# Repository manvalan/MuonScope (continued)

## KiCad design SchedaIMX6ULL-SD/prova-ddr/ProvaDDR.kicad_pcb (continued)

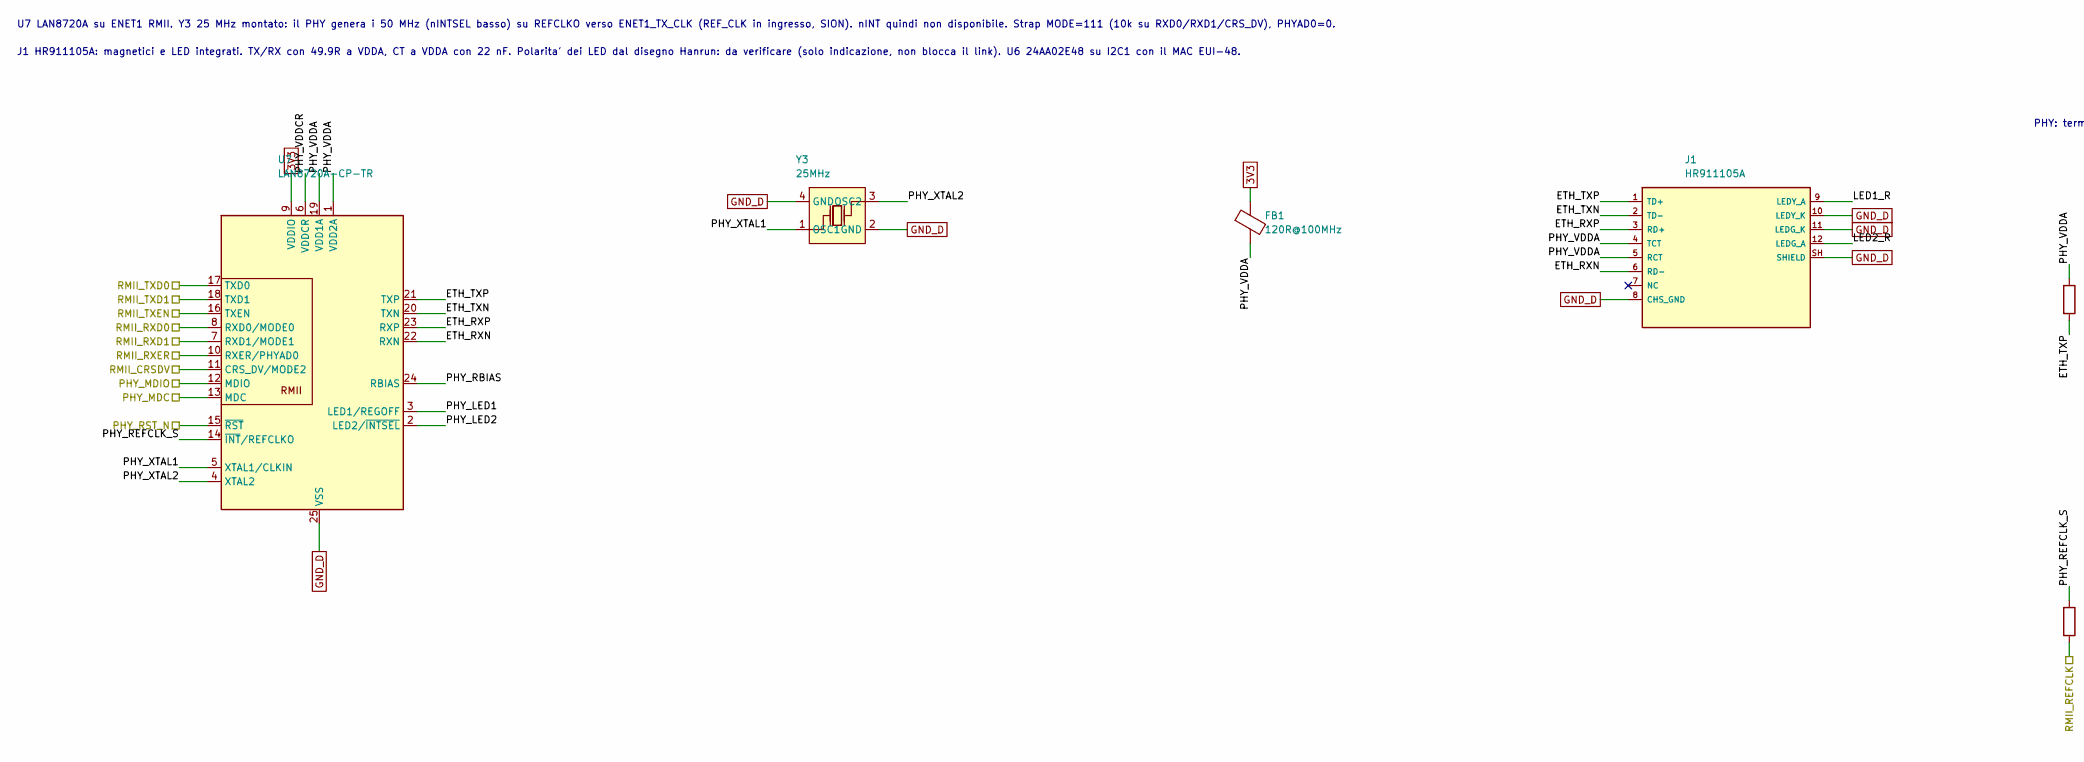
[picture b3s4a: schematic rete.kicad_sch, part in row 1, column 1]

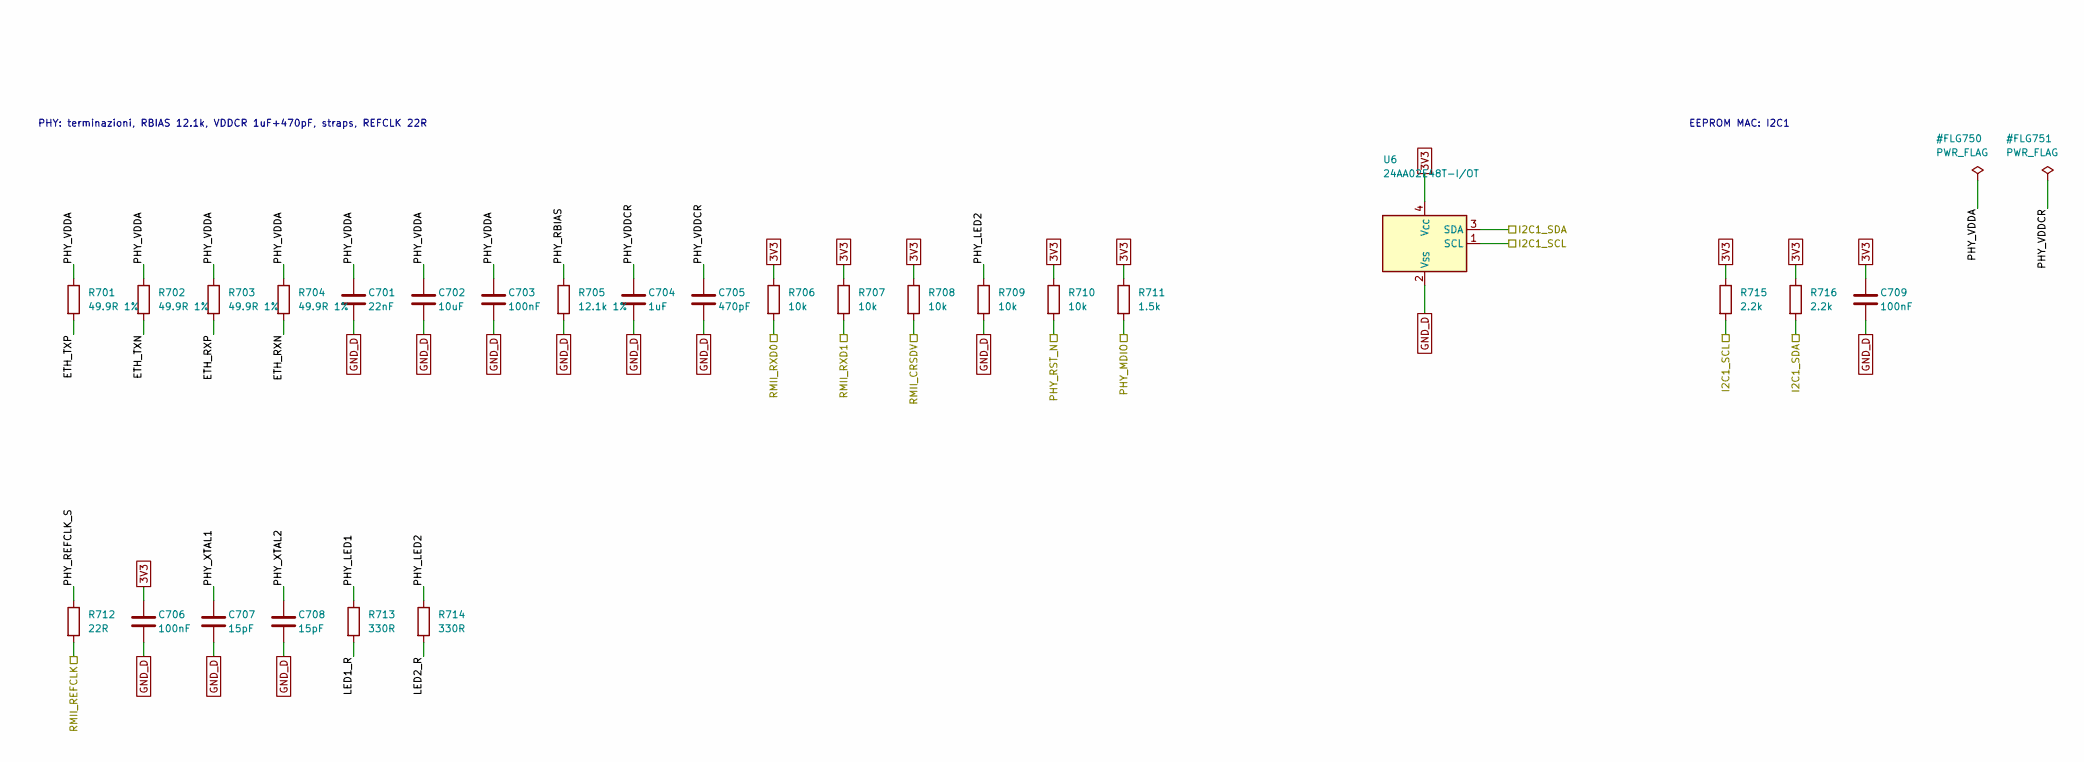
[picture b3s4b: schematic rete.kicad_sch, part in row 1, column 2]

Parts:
C701: 22nF; C_0603_1608Metric
C702: 10uF; C_0805_2012Metric
C703, C706, C709: 100nF; C_0603_1608Metric
C704: 1uF; C_0603_1608Metric
C705: 470pF; C_0603_1608Metric
C707, C708: 15pF; C_0603_1608Metric
FB1: 120R@100MHz; L_0603_1608Metric; MPN BLM18PG121SN1D
J1: HR911105A; RJ45_Hanrun_HR911105A_Horizontal; MPN HR911105A; LCSC C12074
R701, R702, R703, R704: 49.9R 1%; R_0603_1608Metric
R705: 12.1k 1%; R_0603_1608Metric
R706, R707, R708, R709, R710: 10k; R_0603_1608Metric
R711: 1.5k; R_0603_1608Metric
R712: 22R; R_0603_1608Metric
R713, R714: 330R; R_0603_1608Metric
R715, R716: 2.2k; R_0603_1608Metric
U6: 24AA02E48T-I/OT; SOT-23-5; MPN 24AA02E48T-I/OT; LCSC C38987
U7: LAN8720A-CP-TR; QFN-24-1EP_4x4mm_P0.5mm_EP2.6x2.6mm; MPN LAN8720A-CP-TR; LCSC C45223
Y3: 25MHz; CRYSTAL-SMD_4P-L3.2-W2.5-BL; MPN X322525MOB4SI; LCSC C9006

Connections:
3V3: C706.1, C709.1, FB1.1, R706.1, R707.1, R708.1, R710.1, R711.1, R715.1, R716.1, U6.4 (V_{CC}), U7.9 (VDDIO); also elsewhere on the board
/CPU/I2C1_SCL: R715.2, U6.1 (SCL); also elsewhere on the board
/CPU/I2C1_SDA: R716.2, U6.3 (SDA); also elsewhere on the board
/CPU/PHY_MDC: U7.13 (MDC); also elsewhere on the board
/CPU/PHY_MDIO: R711.2, U7.12 (MDIO); also elsewhere on the board
/CPU/PHY_RST_N: R710.2, U7.15 (~RST); also elsewhere on the board
/CPU/RMII_CRSDV: R708.2, U7.11 (CRS_DV/MODE2); also elsewhere on the board
/CPU/RMII_REFCLK: R712.2; also elsewhere on the board
/CPU/RMII_RXD0: R706.2, U7.8 (RXD0/MODE0); also elsewhere on the board
/CPU/RMII_RXD1: R707.2, U7.7 (RXD1/MODE1); also elsewhere on the board
/CPU/RMII_RXER: U7.10 (RXER/PHYAD0); also elsewhere on the board
/CPU/RMII_TXD0: U7.17 (TXD0); also elsewhere on the board
/CPU/RMII_TXD1: U7.18 (TXD1); also elsewhere on the board
/CPU/RMII_TXEN: U7.16 (TXEN); also elsewhere on the board
/Rete/ETH_RXN: J1.6 (RD-), R704.2, U7.22 (RXN)
/Rete/ETH_RXP: J1.3 (RD+), R703.2, U7.23 (RXP)
/Rete/ETH_TXN: J1.2 (TD-), R702.2, U7.20 (TXN)
/Rete/ETH_TXP: J1.1 (TD+), R701.2, U7.21 (TXP)
/Rete/LED1_R: J1.9 (LEDY_A), R713.2
/Rete/LED2_R: J1.12 (LEDG_A), R714.2
/Rete/PHY_LED1: R713.1, U7.3 (LED1/REGOFF)
/Rete/PHY_LED2: R709.1, R714.1, U7.2 (LED2/~INTSEL)
/Rete/PHY_RBIAS: R705.1, U7.24 (RBIAS)
/Rete/PHY_REFCLK_S: R712.1, U7.14 (~INT/REFCLKO)
/Rete/PHY_VDDA: C701.1, C702.1, C703.1, FB1.2, J1.4 (TCT), J1.5 (RCT), R701.1, R702.1, R703.1, R704.1, U7.1 (VDD2A), U7.19 (VDD1A)
/Rete/PHY_VDDCR: C704.1, C705.1, U7.6 (VDDCR)
/Rete/PHY_XTAL1: C707.1, U7.5 (XTAL1/CLKIN), Y3.1 (OSC1)
/Rete/PHY_XTAL2: C708.1, U7.4 (XTAL2), Y3.3 (OSC2)
GND_D: C701.2, C702.2, C703.2, C704.2, C705.2, C706.2, C707.2, C708.2, C709.2, J1.8 (CHS_GND), J1.10 (LEDY_K), J1.11 (LEDG_K), J1.SH (SHIELD), R705.2, R709.2, U6.2 (V_{SS}), U7.25 (VSS), Y3.2 (GND), Y3.4 (GND); also elsewhere on the board

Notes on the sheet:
U7 LAN8720A su ENET1 RMII. Y3 25 MHz montato: il PHY genera i 50 MHz (nINTSEL basso) su REFCLKO verso ENET1_TX_CLK (REF_CLK in ingresso, SION). nINT quindi non disponibile. Strap MODE=111 (10k su RXD0/RXD1/CRS_DV), PHYAD0=0.
J1 HR911105A: magnetici e LED integrati. TX/RX con 49.9R a VDDA, CT a VDDA con 22 nF. Polarita' dei LED dal disegno Hanrun: da verificare (solo indicazione, non blocca il link). U6 24AA02E48 su I2C1 con il MAC EUI-48.
PHY: terminazioni, RBIAS 12.1k, VDDCR 1uF+470pF, straps, REFCLK 22R
EEPROM MAC: I2C1

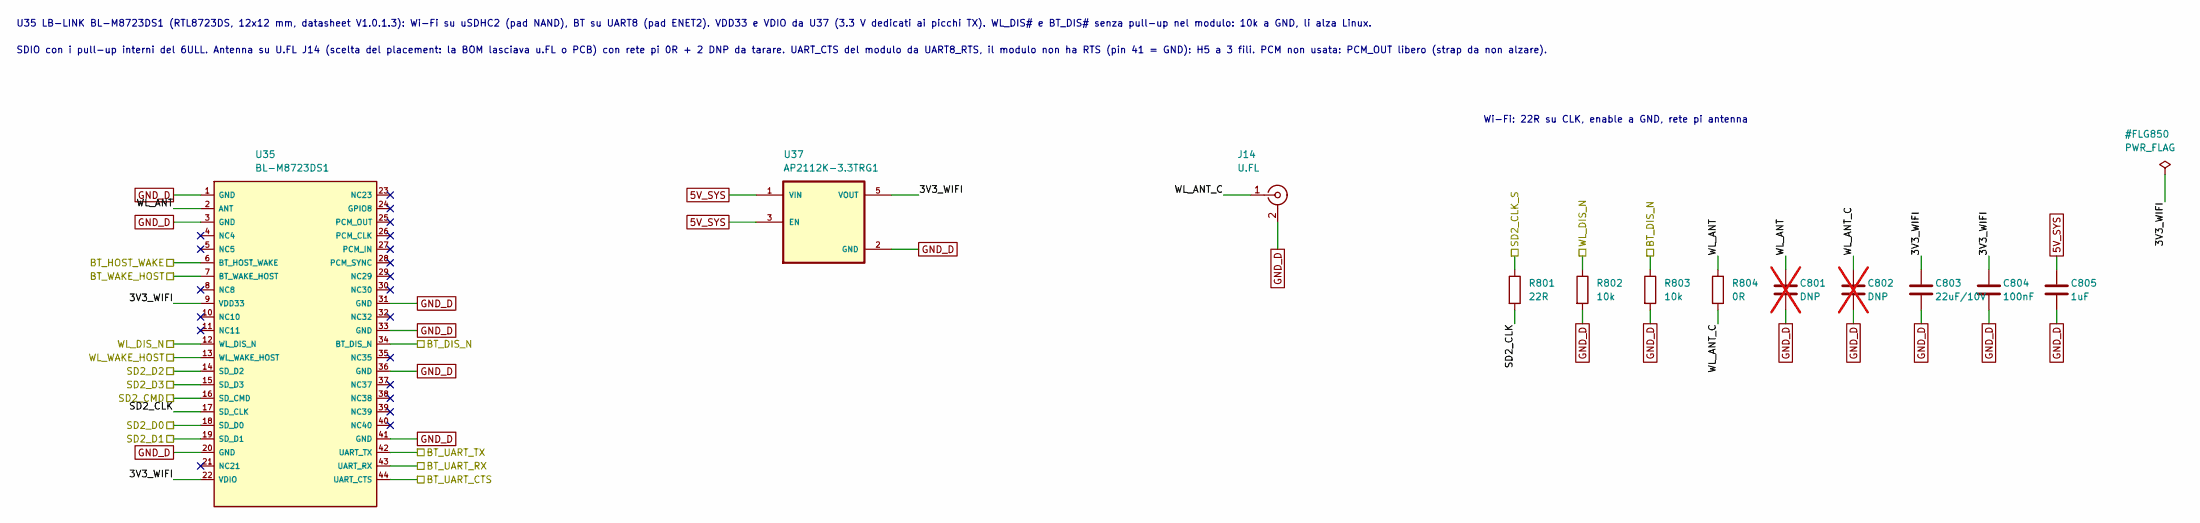
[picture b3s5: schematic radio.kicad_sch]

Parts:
C801, C802: DNP; C_0603_1608Metric; not fitted
C803: 22uF/10V; C_0805_2012Metric
C804: 100nF; C_0603_1608Metric
C805: 1uF; C_0603_1608Metric
J14: U.FL; U.FL_Hirose_U.FL-R-SMT-1_Vertical
R801: 22R; R_0603_1608Metric
R802, R803: 10k; R_0603_1608Metric
R804: 0R; R_0603_1608Metric
U35: BL-M8723DS1; LB-LINK_BL-M8723DS1_LGA-44_12x12mm; MPN BL-M8723DS1
U37: AP2112K-3.3TRG1; SOT95P285X140-5N; MPN AP2112K-3.3TRG1; LCSC C51118

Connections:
5V_SYS: C805.1, U37.1 (VIN), U37.3 (EN); also elsewhere on the board
/CPU/BT_DIS_N: R803.1, U35.34 (BT_DIS_N); also elsewhere on the board
/CPU/BT_HOST_WAKE: U35.6 (BT_HOST_WAKE); also elsewhere on the board
/CPU/BT_UART_CTS: U35.44 (UART_CTS); also elsewhere on the board
/CPU/BT_UART_RX: U35.43 (UART_RX); also elsewhere on the board
/CPU/BT_UART_TX: U35.42 (UART_TX); also elsewhere on the board
/CPU/BT_WAKE_HOST: U35.7 (BT_WAKE_HOST); also elsewhere on the board
/CPU/SD2_CLK_S: R801.1; also elsewhere on the board
/CPU/SD2_CMD: U35.16 (SD_CMD); also elsewhere on the board
/CPU/SD2_D0: U35.18 (SD_D0); also elsewhere on the board
/CPU/SD2_D1: U35.19 (SD_D1); also elsewhere on the board
/CPU/SD2_D2: U35.14 (SD_D2); also elsewhere on the board
/CPU/SD2_D3: U35.15 (SD_D3); also elsewhere on the board
/CPU/WL_DIS_N: R802.1, U35.12 (WL_DIS_N); also elsewhere on the board
/CPU/WL_WAKE_HOST: U35.13 (WL_WAKE_HOST); also elsewhere on the board
/Radio/3V3_WIFI: C803.1, C804.1, U35.9 (VDD33), U35.22 (VDIO), U37.5 (VOUT)
/Radio/SD2_CLK: R801.2, U35.17 (SD_CLK)
/Radio/WL_ANT: C801.1, R804.1, U35.2 (ANT)
/Radio/WL_ANT_C: C802.1, J14.1 (In), R804.2
GND_D: C801.2, C802.2, C803.2, C804.2, C805.2, J14.2 (Ext), R802.2, R803.2, U35.1 (GND), U35.3 (GND), U35.20 (GND), U35.31 (GND), U35.33 (GND), U35.36 (GND), U35.41 (GND), U37.2 (GND); also elsewhere on the board

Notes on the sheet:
U35 LB-LINK BL-M8723DS1 (RTL8723DS, 12x12 mm, datasheet V1.0.1.3): Wi-Fi su uSDHC2 (pad NAND), BT su UART8 (pad ENET2). VDD33 e VDIO da U37 (3.3 V dedicati ai picchi TX). WL_DIS# e BT_DIS# senza pull-up nel modulo: 10k a GND, li alza Linux.
SDIO con i pull-up interni del 6ULL. Antenna su U.FL J14 (scelta del placement: la BOM lasciava u.FL o PCB) con rete pi 0R + 2 DNP da tarare. UART_CTS del modulo da UART8_RTS, il modulo non ha RTS (pin 41 = GND): H5 a 3 fili. PCM non usata: PCM_OUT libero (strap da non alzare).
Wi-Fi: 22R su CLK, enable a GND, rete pi antenna

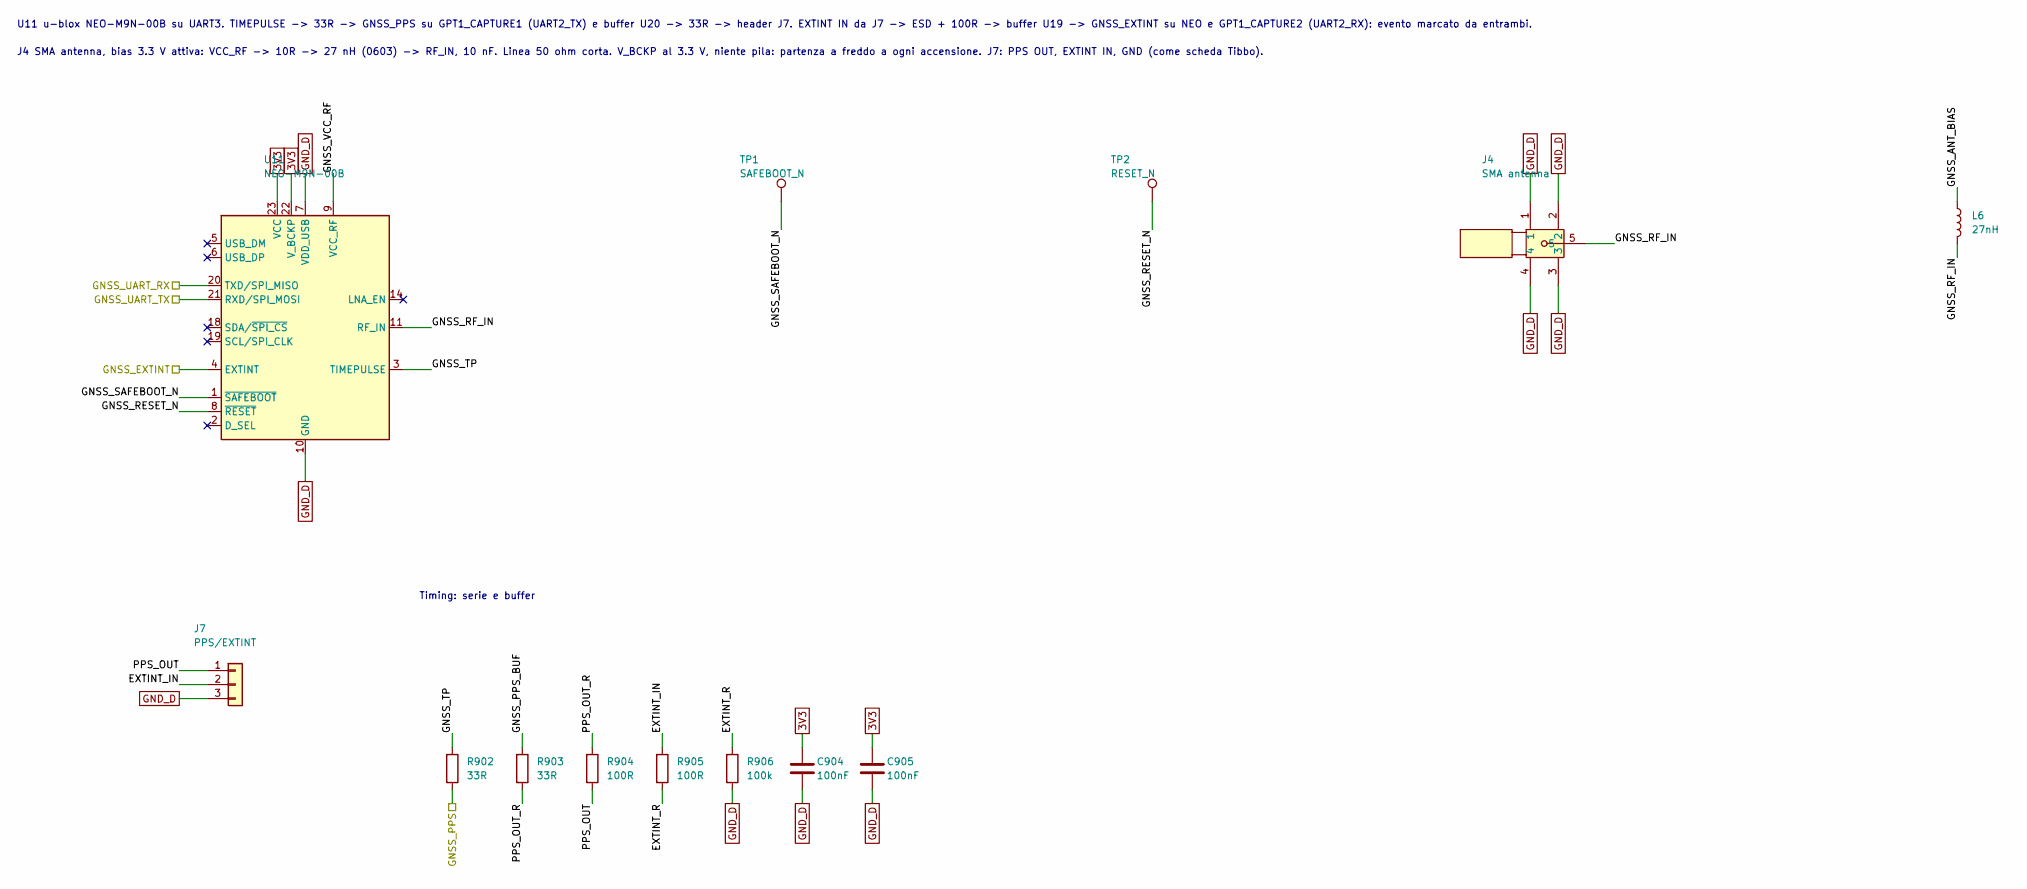
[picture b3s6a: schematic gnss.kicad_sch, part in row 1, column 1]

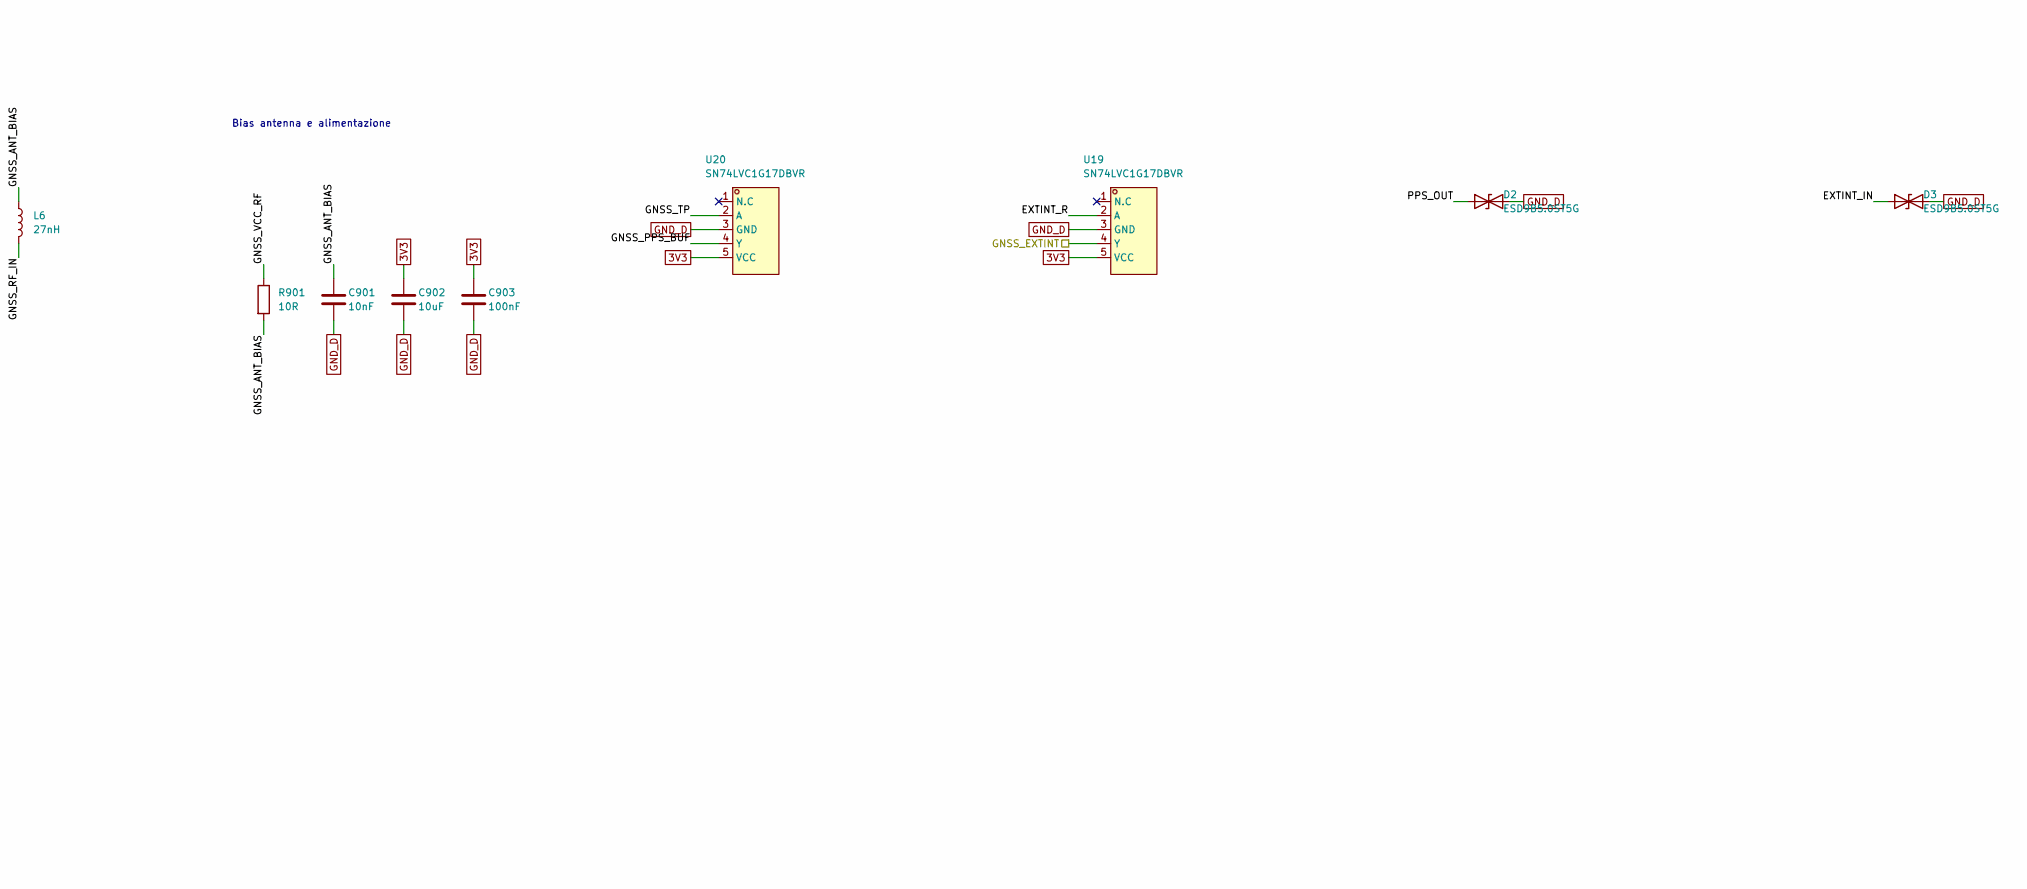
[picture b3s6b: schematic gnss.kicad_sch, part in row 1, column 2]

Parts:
C901: 10nF; C_0603_1608Metric
C902: 10uF; C_0805_2012Metric
C903, C904, C905: 100nF; C_0603_1608Metric
D2, D3: ESD9B5.0ST5G; SODFL1006X40N; MPN ESD9B5.0ST5G; LCSC C111566
J4: SMA antenna; SMA-SMD_BWSMA-KE-P001; MPN BWSMA-KE-P001; LCSC C496550
J7: PPS/EXTINT; PinHeader_1x03_P2.54mm_Vertical; MPN 2.54-1*3P; LCSC C49257
L6: 27nH; L_0603_1608Metric
R901: 10R; R_0603_1608Metric
R902, R903: 33R; R_0603_1608Metric
R904, R905: 100R; R_0603_1608Metric
R906: 100k; R_0603_1608Metric
TP1: SAFEBOOT_N; TestPoint_Pad_D1.0mm
TP2: RESET_N; TestPoint_Pad_D1.0mm
U11: NEO-M9N-00B; ublox_NEO; MPN NEO-M9N-00B
U19, U20: SN74LVC1G17DBVR; SOT-23-5_L3.0-W1.7-P0.95-LS2.8-BR; MPN SN74LVC1G17DBVR; LCSC C7836

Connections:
3V3: C902.1, C903.1, C904.1, C905.1, U11.22 (V_BCKP), U11.23 (VCC), U19.5 (VCC), U20.5 (VCC); also elsewhere on the board
/CPU/GNSS_EXTINT: U11.4 (EXTINT), U19.4 (Y); also elsewhere on the board
/CPU/GNSS_PPS: R902.2; also elsewhere on the board
/CPU/GNSS_UART_RX: U11.20 (TXD/SPI_MISO); also elsewhere on the board
/CPU/GNSS_UART_TX: U11.21 (RXD/SPI_MOSI); also elsewhere on the board
/GNSS/EXTINT_IN: D3.1 (A1), J7.2, R905.1
/GNSS/EXTINT_R: R905.2, R906.1, U19.2 (A)
/GNSS/GNSS_ANT_BIAS: C901.1, L6.1, R901.2
/GNSS/GNSS_PPS_BUF: R903.1, U20.4 (Y)
/GNSS/GNSS_RESET_N: TP2.1, U11.8 (~RESET)
/GNSS/GNSS_RF_IN: J4.5, L6.2, U11.11 (RF_IN)
/GNSS/GNSS_SAFEBOOT_N: TP1.1, U11.1 (~SAFEBOOT)
/GNSS/GNSS_TP: R902.1, U11.3 (TIMEPULSE), U20.2 (A)
/GNSS/GNSS_VCC_RF: R901.1, U11.9 (VCC_RF)
/GNSS/PPS_OUT: D2.1 (A1), J7.1, R904.2
/GNSS/PPS_OUT_R: R903.2, R904.1
GND_D: C901.2, C902.2, C903.2, C904.2, C905.2, D2.2 (A2), D3.2 (A2), J4.1, J4.2, J4.3, J4.4, J7.3, R906.2, U11.7 (VDD_USB), U11.10 (GND), U11.12 (GND), U11.13 (GND), U11.24 (GND), U19.3 (GND), U20.3 (GND); also elsewhere on the board

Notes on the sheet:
U11 u-blox NEO-M9N-00B su UART3. TIMEPULSE -> 33R -> GNSS_PPS su GPT1_CAPTURE1 (UART2_TX) e buffer U20 -> 33R -> header J7. EXTINT IN da J7 -> ESD + 100R -> buffer U19 -> GNSS_EXTINT su NEO e GPT1_CAPTURE2 (UART2_RX): evento marcato da entrambi.
J4 SMA antenna, bias 3.3 V attiva: VCC_RF -> 10R -> 27 nH (0603) -> RF_IN, 10 nF. Linea 50 ohm corta. V_BCKP al 3.3 V, niente pila: partenza a freddo a ogni accensione. J7: PPS OUT, EXTINT IN, GND (come scheda Tibbo).
Bias antenna e alimentazione
Timing: serie e buffer

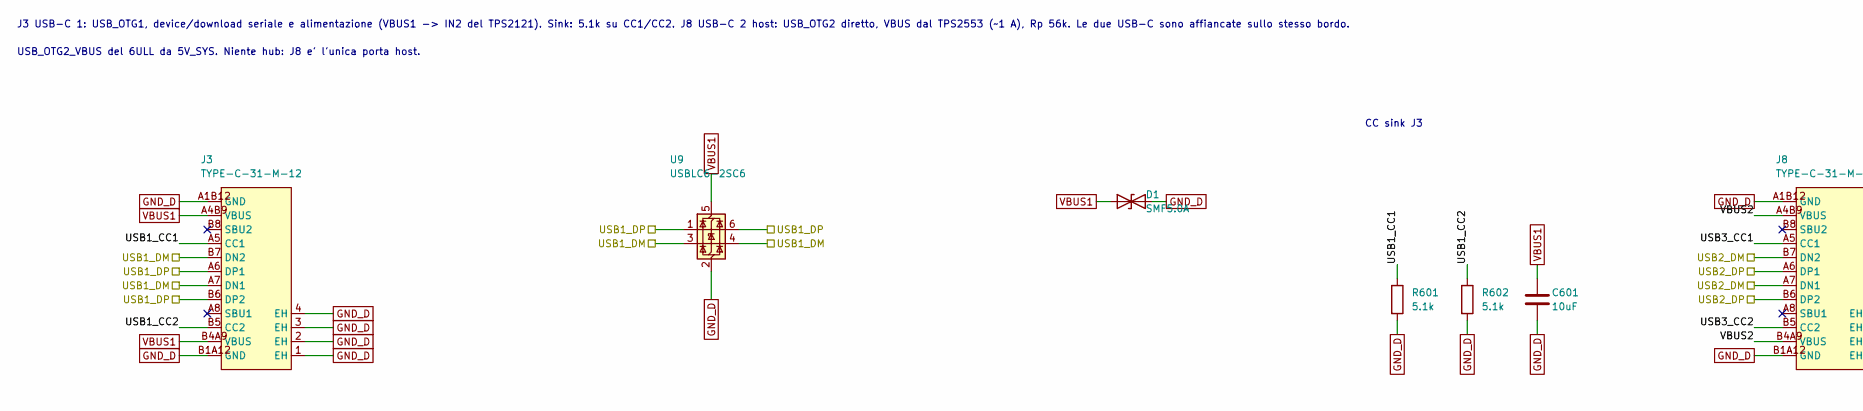
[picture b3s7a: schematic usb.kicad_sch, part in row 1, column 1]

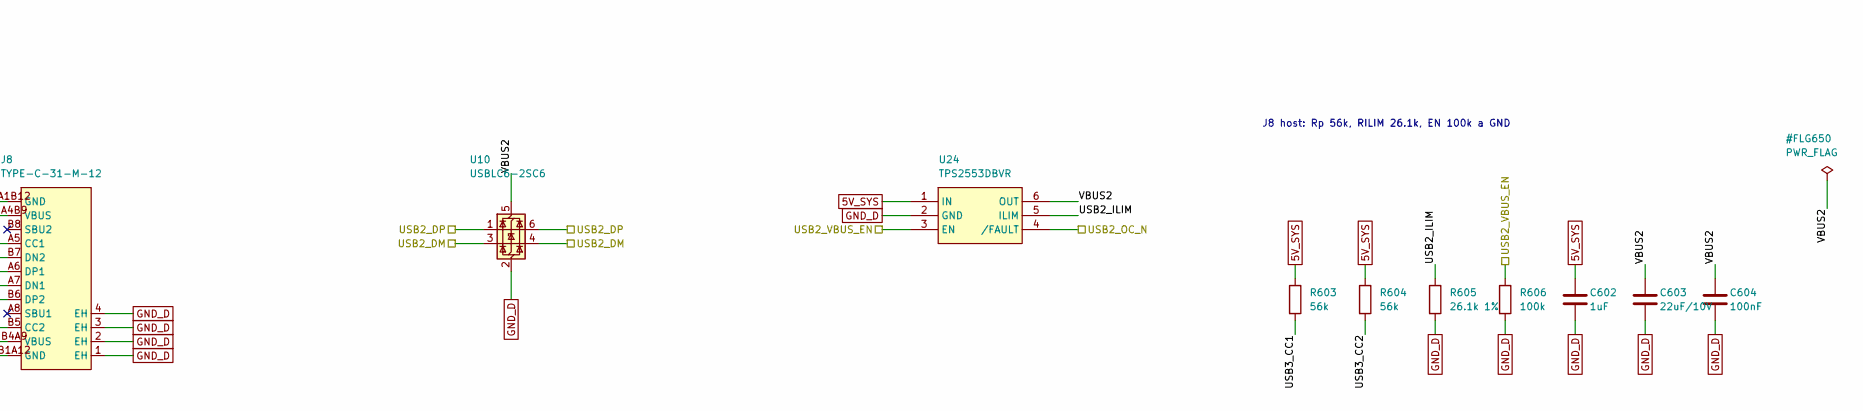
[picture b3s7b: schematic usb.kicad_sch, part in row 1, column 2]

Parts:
C601: 10uF; C_0805_2012Metric
C602: 1uF; C_0603_1608Metric
C603: 22uF/10V; C_1206_3216Metric
C604: 100nF; C_0603_1608Metric
D1: SMF5.0A; D_SMF; MPN SMF5.0A; LCSC C151296
J3, J8: TYPE-C-31-M-12; USB-C_SMD-TYPE-C-31-M-12_1; MPN TYPE-C-31-M-12; LCSC C165948
R601, R602: 5.1k; R_0603_1608Metric
R603, R604: 56k; R_0603_1608Metric
R605: 26.1k 1%; R_0603_1608Metric
R606: 100k; R_0603_1608Metric
U9, U10: USBLC6-2SC6; SOT-23-6; MPN USBLC6-2SC6; LCSC C7519
U24: TPS2553DBVR; TPS2553DBVR_SOT-23-6_L2.9-W1.6-P0.95-LS2.8-BR; MPN TPS2553DBVR; LCSC C55266

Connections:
5V_SYS: C602.1, R603.1, R604.1, U24.1 (IN); also elsewhere on the board
/CPU/USB1_DM: J3.A7 (DN1), J3.B7 (DN2), U9.3 (I/O2), U9.4 (I/O2); also elsewhere on the board
/CPU/USB1_DP: J3.A6 (DP1), J3.B6 (DP2), U9.1 (I/O1), U9.6 (I/O1); also elsewhere on the board
/CPU/USB2_DM: J8.A7 (DN1), J8.B7 (DN2), U10.3 (I/O2), U10.4 (I/O2); also elsewhere on the board
/CPU/USB2_DP: J8.A6 (DP1), J8.B6 (DP2), U10.1 (I/O1), U10.6 (I/O1); also elsewhere on the board
/CPU/USB2_OC_N: U24.4 (/FAULT); also elsewhere on the board
/CPU/USB2_VBUS_EN: R606.1, U24.3 (EN); also elsewhere on the board
/USB/USB1_CC1: J3.A5 (CC1), R601.1
/USB/USB1_CC2: J3.B5 (CC2), R602.1
/USB/USB2_ILIM: R605.1, U24.5 (ILIM)
/USB/USB3_CC1: J8.A5 (CC1), R603.2
/USB/USB3_CC2: J8.B5 (CC2), R604.2
/USB/VBUS2: C603.1, C604.1, J8.A4B9 (VBUS), J8.B4A9 (VBUS), U10.5 (VBUS), U24.6 (OUT)
GND_D: C601.2, C602.2, C603.2, C604.2, D1.2 (A2), J3.1 (EH), J3.2 (EH), J3.3 (EH), J3.4 (EH), J3.A1B12 (GND), J3.B1A12 (GND), J8.1 (EH), J8.2 (EH), J8.3 (EH), J8.4 (EH), J8.A1B12 (GND), J8.B1A12 (GND), R601.2, R602.2, R605.2, R606.2, U9.2 (GND), U10.2 (GND), U24.2 (GND); also elsewhere on the board
VBUS1: C601.1, D1.1 (A1), J3.A4B9 (VBUS), J3.B4A9 (VBUS), U9.5 (VBUS); also elsewhere on the board

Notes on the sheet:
J3 USB-C 1: USB_OTG1, device/download seriale e alimentazione (VBUS1 -> IN2 del TPS2121). Sink: 5.1k su CC1/CC2. J8 USB-C 2 host: USB_OTG2 diretto, VBUS dal TPS2553 (~1 A), Rp 56k. Le due USB-C sono affiancate sullo stesso bordo.
USB_OTG2_VBUS del 6ULL da 5V_SYS. Niente hub: J8 e' l'unica porta host.
CC sink J3
J8 host: Rp 56k, RILIM 26.1k, EN 100k a GND

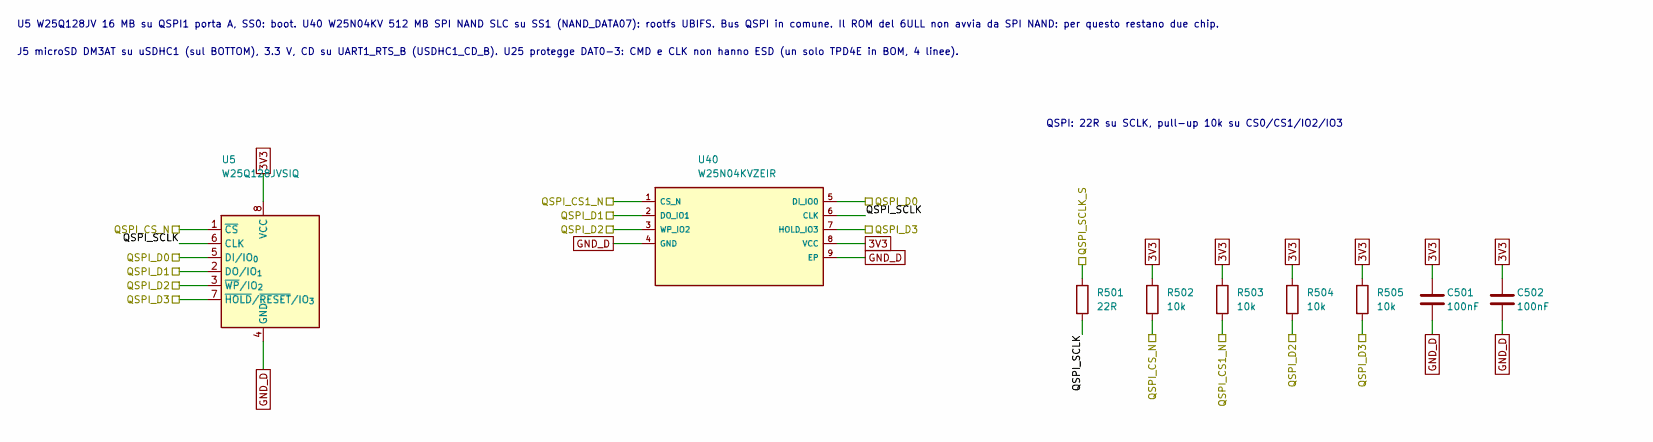
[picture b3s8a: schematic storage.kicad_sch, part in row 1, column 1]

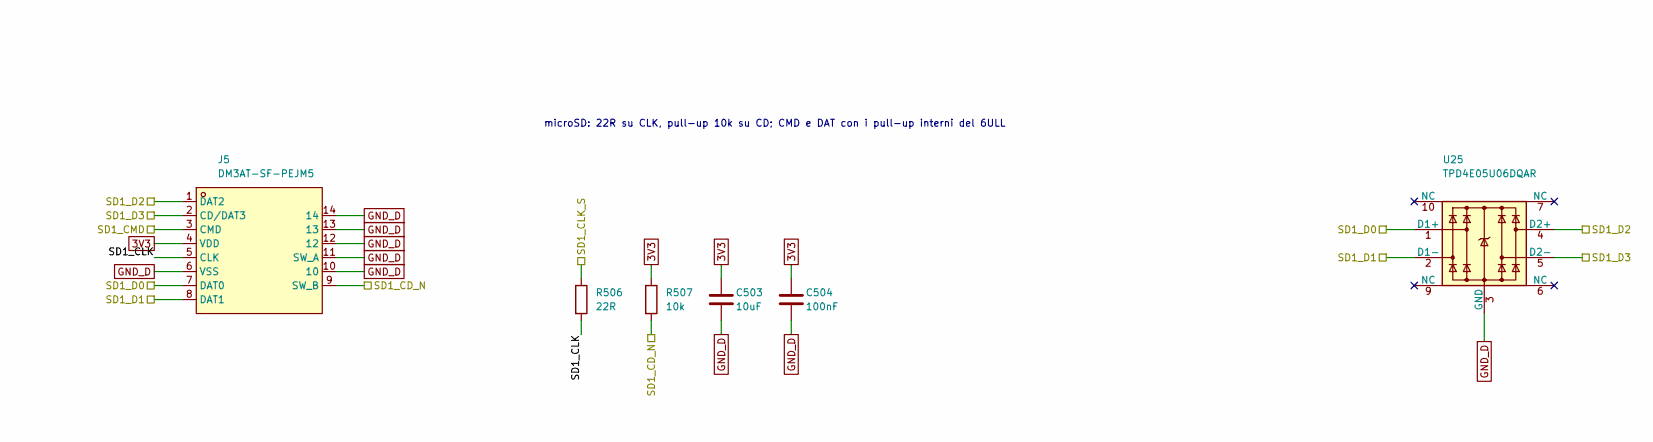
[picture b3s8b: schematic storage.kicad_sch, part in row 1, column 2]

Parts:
C501, C502, C504: 100nF; C_0603_1608Metric
C503: 10uF; C_0805_2012Metric
J5: DM3AT-SF-PEJM5; SD-SMD_DM3AT-SF-PEJM5; MPN DM3AT-SF-PEJM5; LCSC C114218
R501, R506: 22R; R_0603_1608Metric
R502, R503, R504, R505, R507: 10k; R_0603_1608Metric
U5: W25Q128JVSIQ; SOIC-8_5.3x5.3mm_P1.27mm; MPN W25Q128JVSIQ; LCSC C97521
U25: TPD4E05U06DQAR; USON-10_2.5x1.0mm_P0.5mm; MPN TPD4E05U06DQAR
U40: W25N04KVZEIR; WSON-8-1EP_8x6mm_P1.27mm_EP3.4x4.3mm; MPN W25N04KVZEIR; LCSC C5342170

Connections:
3V3: C501.1, C502.1, C503.1, C504.1, J5.4 (VDD), R502.1, R503.1, R504.1, R505.1, R507.1, U5.8 (VCC), U40.8 (VCC); also elsewhere on the board
/CPU/QSPI_CS1_N: R503.2, U40.1 (CS_N); also elsewhere on the board
/CPU/QSPI_CS_N: R502.2, U5.1 (~CS); also elsewhere on the board
/CPU/QSPI_D0: U5.5 (DI/IO_{0}), U40.5 (DI_IO0); also elsewhere on the board
/CPU/QSPI_D1: U5.2 (DO/IO_{1}), U40.2 (DO_IO1); also elsewhere on the board
/CPU/QSPI_D2: R504.2, U5.3 (~WP/IO_{2}), U40.3 (WP_IO2); also elsewhere on the board
/CPU/QSPI_D3: R505.2, U5.7 (~HOLD/~RESET/IO_{3}), U40.7 (HOLD_IO3); also elsewhere on the board
/CPU/QSPI_SCLK_S: R501.1; also elsewhere on the board
/CPU/SD1_CD_N: J5.9 (SW_B), R507.2; also elsewhere on the board
/CPU/SD1_CLK_S: R506.1; also elsewhere on the board
/CPU/SD1_CMD: J5.3 (CMD); also elsewhere on the board
/CPU/SD1_D0: J5.7 (DAT0), U25.1 (D1+); also elsewhere on the board
/CPU/SD1_D1: J5.8 (DAT1), U25.2 (D1-); also elsewhere on the board
/CPU/SD1_D2: J5.1 (DAT2), U25.4 (D2+); also elsewhere on the board
/CPU/SD1_D3: J5.2 (CD/DAT3), U25.5 (D2-); also elsewhere on the board
/Storage/QSPI_SCLK: R501.2, U5.6 (CLK), U40.6 (CLK)
/Storage/SD1_CLK: J5.5 (CLK), R506.2
GND_D: C501.2, C502.2, C503.2, C504.2, J5.6 (VSS), J5.10, J5.11 (SW_A), J5.12, J5.13, J5.14, U5.4 (GND), U25.3 (GND), U25.8 (GND), U40.4 (GND), U40.9 (EP); also elsewhere on the board

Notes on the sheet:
U5 W25Q128JV 16 MB su QSPI1 porta A, SS0: boot. U40 W25N04KV 512 MB SPI NAND SLC su SS1 (NAND_DATA07): rootfs UBIFS. Bus QSPI in comune. Il ROM del 6ULL non avvia da SPI NAND: per questo restano due chip.
J5 microSD DM3AT su uSDHC1 (sul BOTTOM), 3.3 V, CD su UART1_RTS_B (USDHC1_CD_B). U25 protegge DAT0-3: CMD e CLK non hanno ESD (un solo TPD4E in BOM, 4 linee).
QSPI: 22R su SCLK, pull-up 10k su CS0/CS1/IO2/IO3
microSD: 22R su CLK, pull-up 10k su CD; CMD e DAT con i pull-up interni del 6ULL

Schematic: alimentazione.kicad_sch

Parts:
C301, C302: 10uF/25V; C_1206_3216Metric
C303: 100nF/50V; C_0603_1608Metric
C304, C308, C313, C321: 100nF; C_0603_1608Metric
C305: 100pF; C_0603_1608Metric
C306, C307, C311, C314: 47uF/10V; C_1206_3216Metric
C309, C310: 1uF/10V; C_0603_1608Metric
C312: 10uF/16V; C_0805_2012Metric
C315, C318: 10uF/10V; C_0805_2012Metric
C316: 470nF; C_0603_1608Metric
C317, C320: 22uF/10V; C_0805_2012Metric
C319: 1uF; C_0603_1608Metric
L1: 3.3uH/8A; L_Coilcraft_XAL6030-XXX; MPN XAL6030-332MEC
L2: 2.2uH/4A; L_Coilcraft_XAL4020-XXX; MPN XAL4020-222
L3, L4: 2.2uH/3A; L_Coilcraft_XAL4020-XXX; MPN XAL4020-222
R301: 169k 1%; R_0603_1608Metric
R302: 36.1k 1%; R_0603_1608Metric
R303, R314, R317, R320: 100k; R_0603_1608Metric
R304: 73.2k 1%; R_0603_1608Metric
R305, R308, R310, R312, R316: 10k 1%; R_0603_1608Metric
R306: 20k; R_0603_1608Metric
R307: 32.4k 1%; R_0603_1608Metric
R309, R311: 46.4k 1%; R_0603_1608Metric
R313: 22.1k 1%; R_0603_1608Metric
R315: 33.2k 1%; R_0603_1608Metric
R318: 150k 1%; R_0603_1608Metric
R319: 120k 1%; R_0603_1608Metric
R321: 133k 1%; R_0603_1608Metric
R322: 100k 1%; R_0603_1608Metric
R323: 1k; R_0603_1608Metric
U17: TPS2121RUXR; IC_TPS2121RUXR; MPN TPS2121RUXR; LCSC C485916
U22: TPS56637RPAR; VQFN-HR-10_L3.0-W3.0_RPA; MPN TPS56637RPAR; LCSC C841386
U23: TPS563201DDCR; TPS563201DDCR_SOT-23-6_L2.9-W1.6-P0.95-LS2.8-BR; MPN TPS563201DDCR; LCSC C116592
U26, U27: TLV62569DBVR; TLV62569DBVR_SOT95P280X145-5N; MPN TLV62569DBVR
U28: TPS3839K33DBZR; SOT-23; MPN TPS3839K33DBZR

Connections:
3V3: C314.1, C321.1, L2.2, R315.1, R317.1, R320.1, U28.3 (VDD); also elsewhere on the board
5V_SYS: C311.1, C312.1, C315.1, C318.1, R314.1, U17.1 (OUT), U17.1_1 (OUT), U17.8 (OUT), U17.8_1 (OUT), U23.3 (VIN), U26.4 (VIN), U27.4 (VIN); also elsewhere on the board
/Alimentazione/5V_BUCK: C306.1, C307.1, C309.1, L1.2, R303.1, R304.1, R306.1, R307.1, R309.1, U17.7 (IN1), U17.7_1 (IN1)
/Alimentazione/BUCK_BST: C304.1, U22.7 (BOOT)
/Alimentazione/BUCK_EN: R301.2, R302.1, U22.1 (EN)
/Alimentazione/BUCK_FB: C305.2, R304.2, R305.1, U22.2 (FB)
/Alimentazione/BUCK_FF: C305.1, R306.2
/Alimentazione/BUCK_PG: R303.2, U22.4 (PG)
/Alimentazione/BUCK_SW: C304.2, L1.1, U22.6 (SW)
/Alimentazione/MUX_ILM: R313.1, U17.10 (ILIM)
/Alimentazione/MUX_OV1: R309.2, R310.1, U17.5 (OV1)
/Alimentazione/MUX_OV2: R311.2, R312.1, U17.4 (OV2)
/Alimentazione/MUX_PR1: R307.2, R308.1, U17.6 (PR1)
/Alimentazione/MUX_SS: C308.1, U17.11 (SS)
/Alimentazione/POR_B: R323.2; also elsewhere on the board
/Alimentazione/POR_DRV: R323.1, U28.2 (~RESET)
/Alimentazione/PWR_SRC_ST: U17.9 (ST); also elsewhere on the board
/Alimentazione/U23_BST: C313.1, U23.6 (VBST)
/Alimentazione/U23_EN: R314.2, U23.5 (EN)
/Alimentazione/U23_FB: R315.2, R316.1, U23.4 (VFB)
/Alimentazione/U23_SW: C313.2, L2.1, U23.2 (SW)
/Alimentazione/U26_EN: C316.1, R317.2, U26.1 (EN)
/Alimentazione/U26_FB: R318.2, R319.1, U26.5 (FB)
/Alimentazione/U26_SW: L3.1, U26.3 (SW)
/Alimentazione/U27_EN: C319.1, R320.2, U27.1 (EN)
/Alimentazione/U27_FB: R321.2, R322.1, U27.5 (FB)
/Alimentazione/U27_SW: L4.1, U27.3 (SW)
GND_D: C301.2, C302.2, C303.2, C306.2, C307.2, C308.2, C309.2, C310.2, C311.2, C312.2, C314.2, C315.2, C316.2, C317.2, C318.2, C319.2, C320.2, C321.2, R302.2, R305.2, R308.2, R310.2, R312.2, R313.2, R316.2, R319.2, R322.2, U17.3 (CP2), U17.12 (GND), U22.3 (AGND), U22.9 (PGND), U23.1 (GND), U26.2 (GND), U27.2 (GND), U28.1 (GND); also elsewhere on the board
V1P4: C320.1, L4.2, R321.1; also elsewhere on the board
V1P35: C317.1, L3.2, R318.1; also elsewhere on the board
VBUS1: C310.1, R311.1, U17.2 (IN2), U17.2_1 (IN2); also elsewhere on the board
VIN_SYS: C301.1, C302.1, C303.1, R301.1, U22.8 (VIN); also elsewhere on the board

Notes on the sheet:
VIN_SYS 12 V dal BUS_POWER -> TPS56637 5 V (U22) -> TPS2121 U17 (IN1 bus con priorita, IN2 VBUS USB-C 1) -> 5V_SYS -> buck 3.3 V (U23), 1.35 V DDR (U26), 1.4 V VDD_SOC_IN (U27).
Sequenza 3.3 -> 1.35 -> 1.4 V a RC sugli EN del TLV62569 (soglia EN max 1.2 V): 100k/470nF circa 21 ms, 100k/1uF circa 45 ms. POR_B dal TPS3839K33 (2.93 V, push-pull) con 1k in serie, cosi' SW1 puo' cortocircuitare POR_B.
Niente pila di backup: VDD_SNVS_IN e V_BCKP del GNSS direttamente al 3.3 V. RTC e dati GNSS si perdono a ogni spegnimento. Passivi 0603 minimo; 47 uF e 10 uF/25 V in 1206, 22 uF e 10 uF in 0805.
TPS56637: EN 169k/36.1k, FB 73.2k/10k = 4.99 V, FF 20k+100pF, MODE aperto = FCCM, 2x47 uF al posto di 4x22 uF
TPS2121 (come RK3568): PR1 4.49 V, OV 5.98 V, ILM 22.1k = 4-5 A, SS 100 nF
U23 3.3 V / 3 A: FB 33.2k/10k = 3.32 V, primo della sequenza
U26 1.35 V DDR: FB 150k/120k (0.6 V x 2.25), EN 100k/470nF da 3V3
U27 1.4 V VDD_SOC_IN: FB 133k/100k = 1.398 V (min 1.375 V, 125 mV sopra VDD_ARM_CAP), EN 100k/1uF da 3V3
POR_B
